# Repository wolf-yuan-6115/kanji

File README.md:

# Kanji

Kanji is an ESP32 based Wi-Fi smart clock. Featuring E-ink display, it can pull weather data, calendar and display realtime clock. It is designed to be a simple and elegant clock that can be placed on a desk. There's also a SHT40 temperature and humidity sensor to provide more information.

Case was not designed and it's intended to just directly use screw as stand.

> Note that display is not here yet because it's going to order seperately.

## Schematic

## Routing

## BOM

| Name | Qty | Total (USD) | Distributor |
| --- | --- | --- | --- |
| WaveShare E-Ink display & Seeed Xiao ESP32-S3 | 1 | $35.00 | Taobao (Like Aliexpress but China version) |
| PCB Assambly | 1 | $44.84 | JLCPCB |
| PCB | 1 | $10.56 | JLCPCB |
| Shipping | 1 | $6.12 | JLCPCB |
| Total | 1 | $96.52 | - |

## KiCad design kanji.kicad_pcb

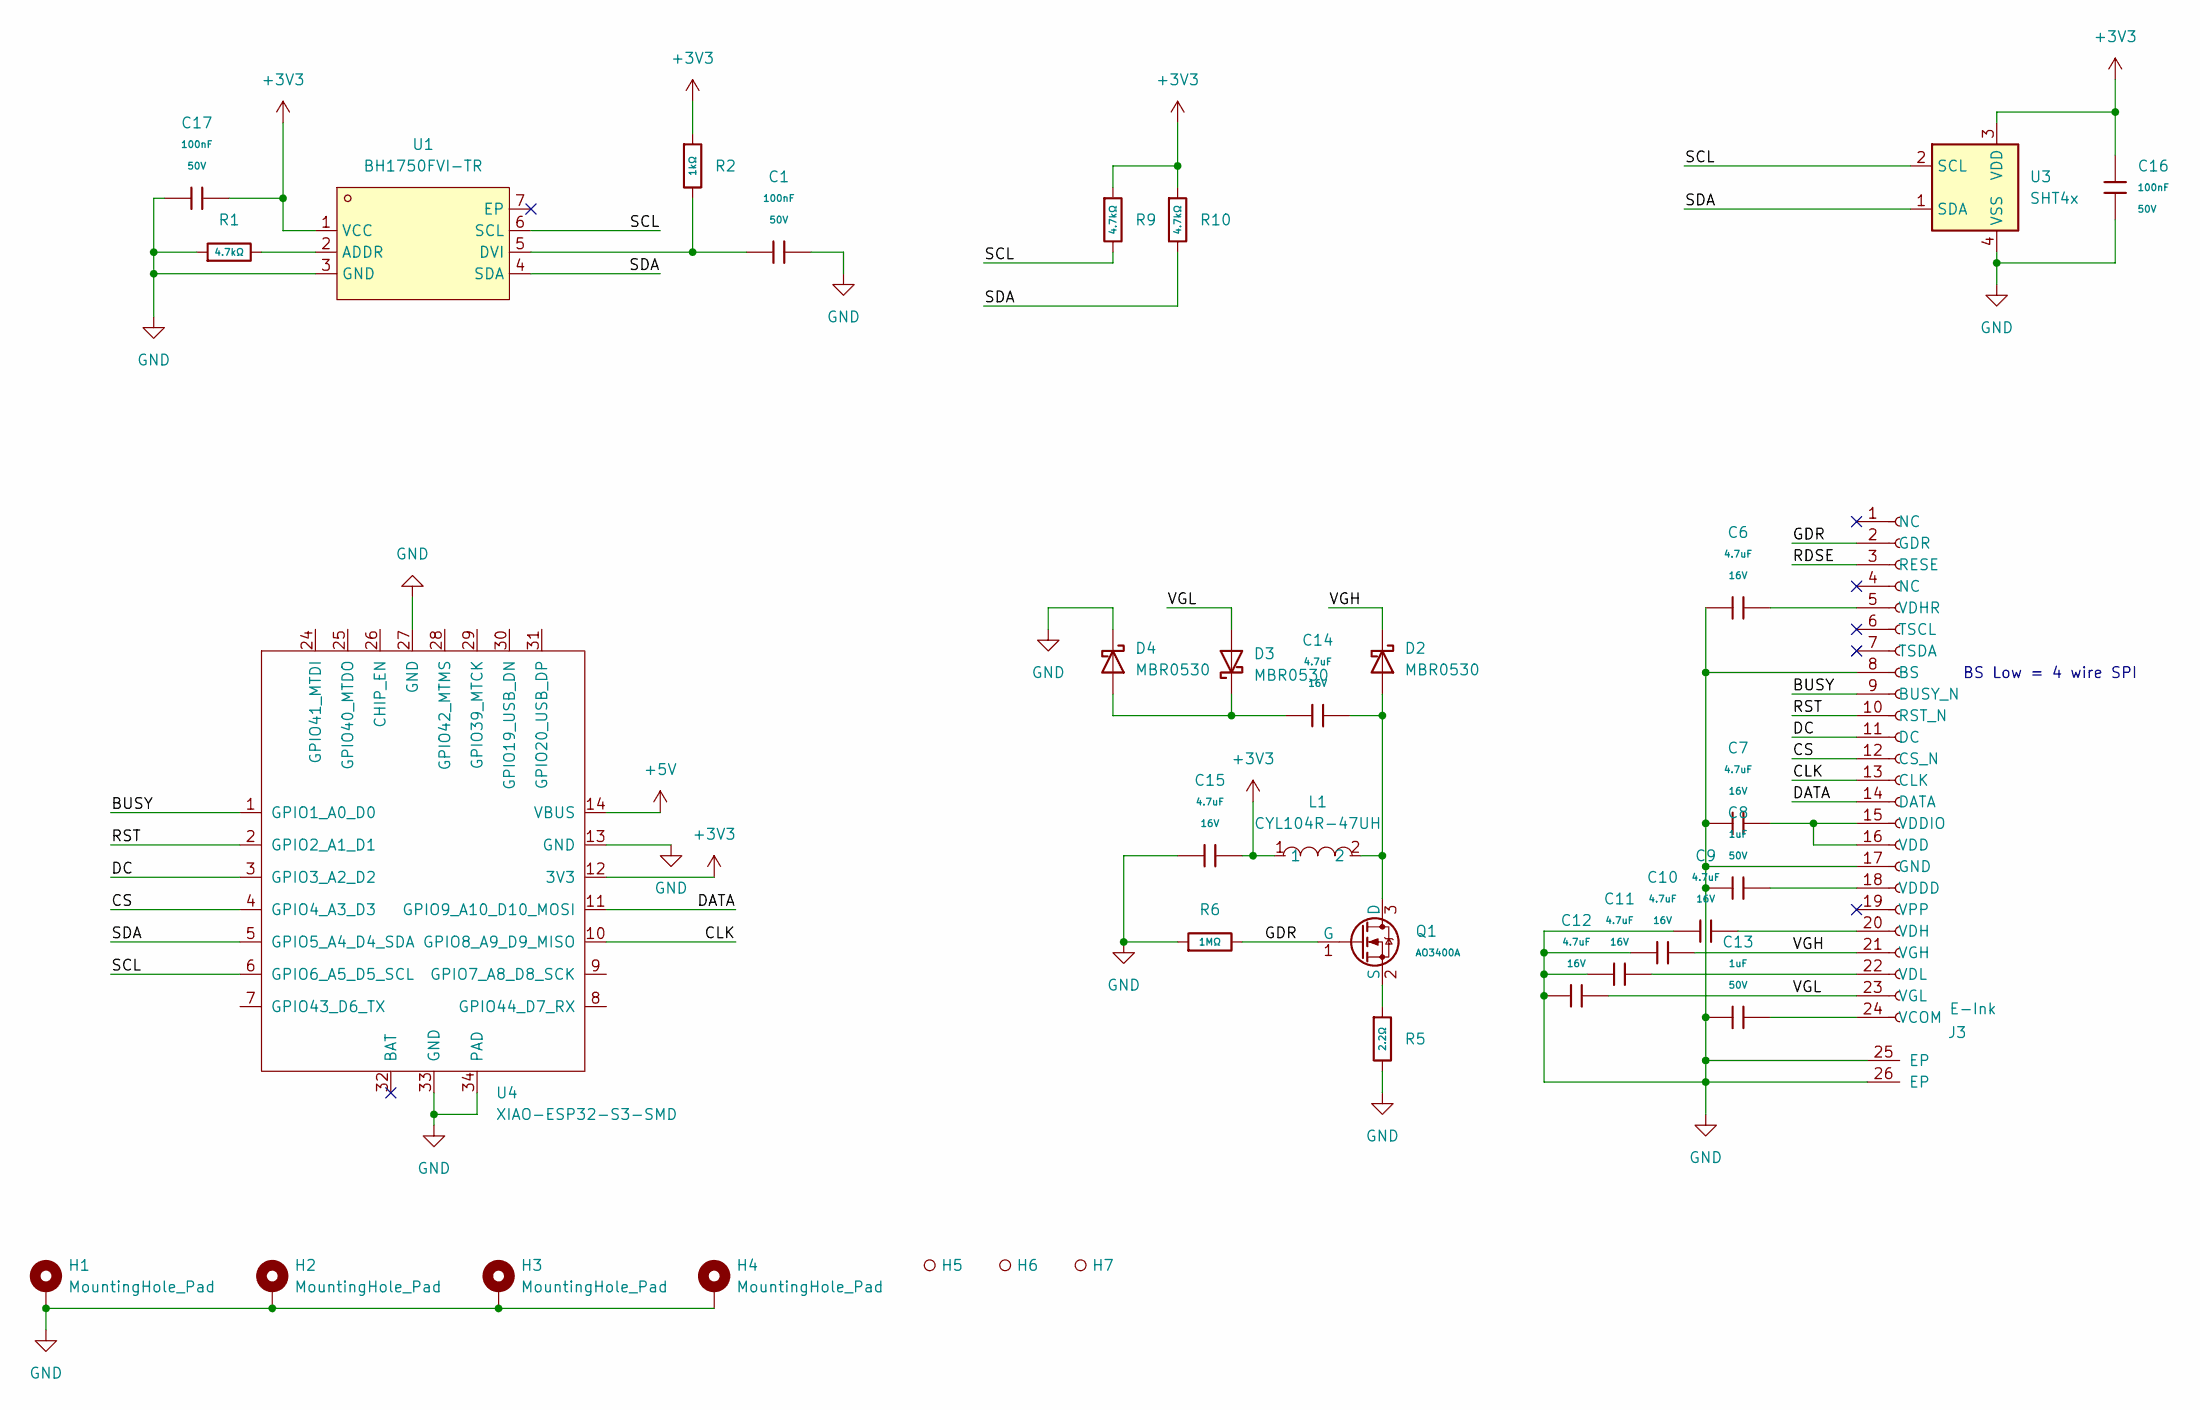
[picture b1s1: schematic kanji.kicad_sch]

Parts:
C1, C16, C17: 100nF; C_0603; Voltage Rated 50V; Tolerance ±10%; Part CC0603KRX7R9BB104; LCSC C14663
C6, C7, C9, C10, C11, C12, C14, C15: 4.7uF; C_0603; Voltage Rated 16V; Tolerance ±10%; Part CL10A475KO8NNNC; LCSC C19666
C8, C13: 1uF; C_0603; Voltage Rated 50V; Tolerance ±10%; Part CL10A105KB8NNNC; LCSC C15849
D2, D3, D4: MBR0530; D_SOD-123
H1, H2, H3, H4: MountingHole_Pad; MountingHole_3.2mm_M3_Pad_Via
H5, H6, H7: Hole_Tooling_JLCPCB
J3: E-Ink; FPC-SMD_AFC07-S24FCC-00
L1: CYL104R-47UH; IND-SMD_L10.5-W10.5; MPN CYL104R-47UH; LCSC Part C7431100
Q1: AO3400A; Q_SOT-23; Part AO3400A; LCSC C20917
R1, R9, R10: 4.7kΩ; R_0603; Overload Voltage (Max) 75V; Tolerance ±1%; Part 0603WAF4701T5E; LCSC C23162
R2: 1kΩ; R_0603; Overload Voltage (Max) 75V; Tolerance ±1%; Part 0603WAF1001T5E; LCSC C21190
R5: 2.2Ω; R_0603; Overload Voltage (Max) 75V; Tolerance ±1%; Part 0603WAF220KT5E; LCSC C22939
R6: 1MΩ; R_0603; Overload Voltage (Max) 75V; Tolerance ±1%; Part 0603WAF1004T5E; LCSC C22935
U1: BH1750FVI-TR; WSOF-6_L2.6-W1.6-P0.50-TL-EP; MPN BH1750FVI-TR; LCSC Part C78960
U3: SHT4x; Sensirion_DFN-4_1.5x1.5mm_P0.8mm_SHT4x_NoCentralPad; LCSC C2909890
U4: XIAO-ESP32-S3-SMD

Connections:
+3V3: C15.2, C16.1, C17.2, L1.1, R2.1, R9.1, R10.1, U1.1 (VCC), U3.3 (VDD), U4.12 (3V3)
+5V: U4.14 (VBUS)
/BUSY: J3.9 (BUSY_N), U4.1 (GPIO1_A0_D0)
/CLK: J3.13 (CLK), U4.10 (GPIO8_A9_D9_MISO)
/CS: J3.12 (CS_N), U4.4 (GPIO4_A3_D3)
/DATA: J3.14 (DATA), U4.11 (GPIO9_A10_D10_MOSI)
/DC: J3.11 (DC), U4.3 (GPIO3_A2_D2)
/GDR: J3.2 (GDR), Q1.1 (G), R6.2
/RDSE: J3.3 (RESE)
/RST: J3.10 (RST_N), U4.2 (GPIO2_A1_D1)
/SCL: R9.2, U1.6 (SCL), U3.2 (SCL), U4.6 (GPIO6_A5_D5_SCL)
/SDA: R10.2, U1.4 (SDA), U3.1 (SDA), U4.5 (GPIO5_A4_D4_SDA)
/VGH: C10.2, D2.1 (K), J3.21 (VGH)
/VGL: C12.2, D3.2 (A), J3.23 (VGL)
GND: C1.2, C6.1, C7.1, C8.1, C9.1, C10.1, C11.1, C12.1, C13.1, C15.1, C16.2, C17.1, D4.1 (K), H1.1 (1_1), H2.1 (1_1), H3.1 (1_1), H4.1 (1_1), J3.8 (BS), J3.17 (GND), J3.25 (EP), J3.26 (EP), R1.1, R5.2, R6.1, U1.3 (GND), U3.4 (VSS), U4.13 (GND), U4.27 (GND), U4.33 (GND), U4.34 (PAD)
unnamed: C14.2, D2.2 (A), L1.2, Q1.3 (D)
unnamed: C14.1, D3.1 (K), D4.2 (A)
unnamed: C13.2, J3.24 (VCOM)
unnamed: C7.2, J3.15 (VDDIO), J3.16 (VDD)
unnamed: C8.2, J3.18 (VDDD)
unnamed: C9.2, J3.20 (VDH)
unnamed: C6.2, J3.5 (VDHR)
unnamed: C11.2, J3.22 (VDL)
unnamed: Q1.2 (S), R5.1
unnamed: R1.2, U1.2 (ADDR)
unnamed: C1.1, R2.2, U1.5 (DVI)

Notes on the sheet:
BS Low = 4 wire SPI

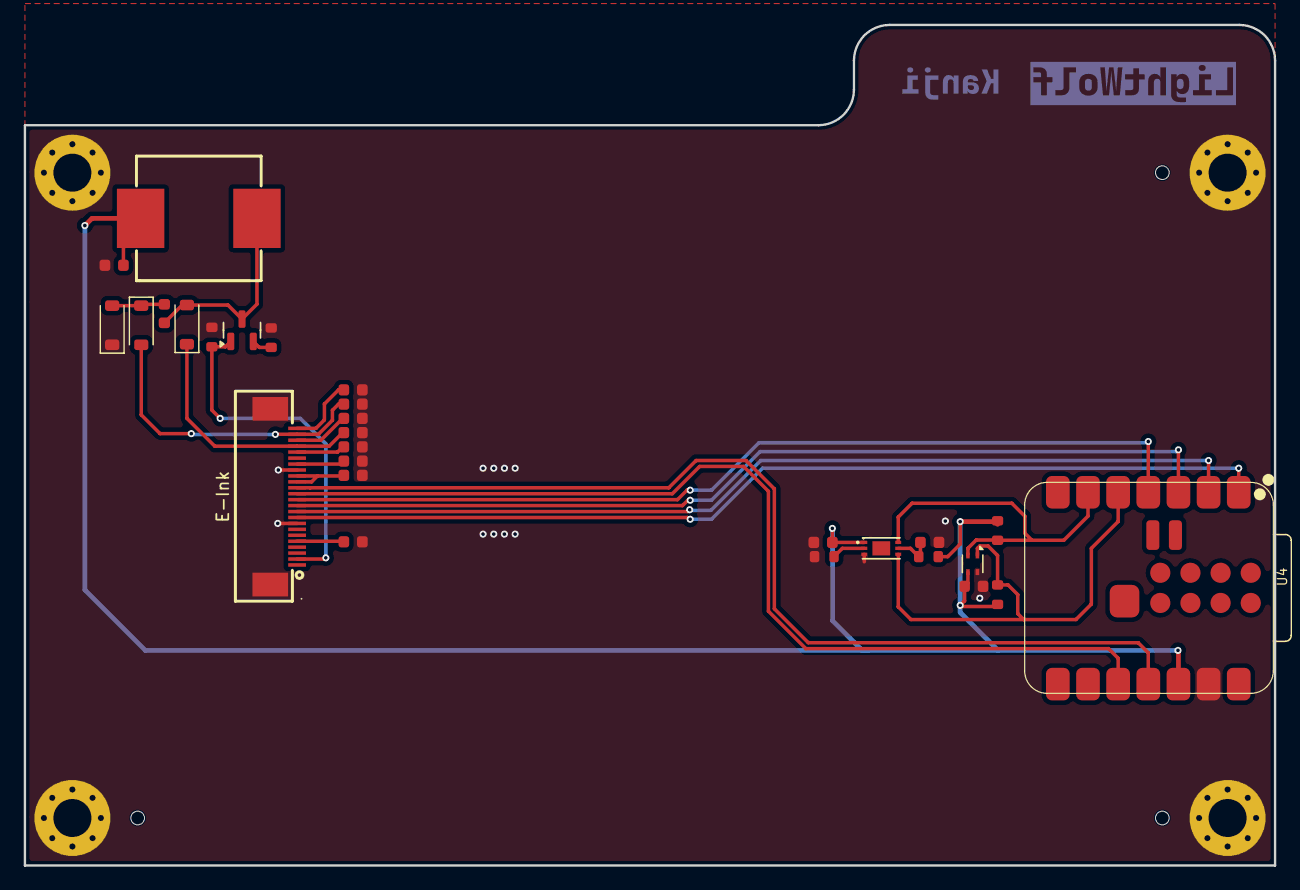
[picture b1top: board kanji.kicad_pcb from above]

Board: 2 copper layers, 105.3 x 70.8 mm, 35 parts (0 on the bottom side), 24 nets.

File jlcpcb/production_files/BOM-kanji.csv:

Comment,Designator,Footprint,LCSC,Quantity
100nF,"C1,C16,C17",C_0603,C14663,3
1MΩ,R6,R_0603,C22935,1
1kΩ,R2,R_0603,C21190,1
1uF,"C13,C8",C_0603,C15849,2
2.2Ω,R5,R_0603,C22939,1
4.7kΩ,"R1,R10,R9",R_0603,C23162,3
4.7uF,"C10,C11,C12,C14,C15,C6,C7,C9",C_0603,C19666,8
AO3400A,Q1,Q_SOT-23,C20917,1
BH1750FVI-TR,U1,WSOF-6_L2.6-W1.6-P0.50-TL-EP,C78960,1
CYL104R-47UH,L1,IND-SMD_L10.5-W10.5,C7431100,1
E-Ink,J3,FPC-SMD_AFC07-S24FCC-00,C11057,1
MBR0530,"D2,D3,D4",D_SOD-123,C77336,3
SHT4x,U3,Sensirion_DFN-4_1.5x1.5mm_P0.8mm_SHT4x_NoCentralPad,C2909890,1

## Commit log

2026-05-18 feat: init design
2026-05-18 feat: add testing firmware
2026-05-18 feat: add gitignore
2026-05-19 feat: add light sensor logic
2026-05-19 feat: add routing image
2026-05-19 feat: add light sensor
2026-05-19 feat: update bom due to new als
2026-05-20 feat: update pio config files for vscode and git
